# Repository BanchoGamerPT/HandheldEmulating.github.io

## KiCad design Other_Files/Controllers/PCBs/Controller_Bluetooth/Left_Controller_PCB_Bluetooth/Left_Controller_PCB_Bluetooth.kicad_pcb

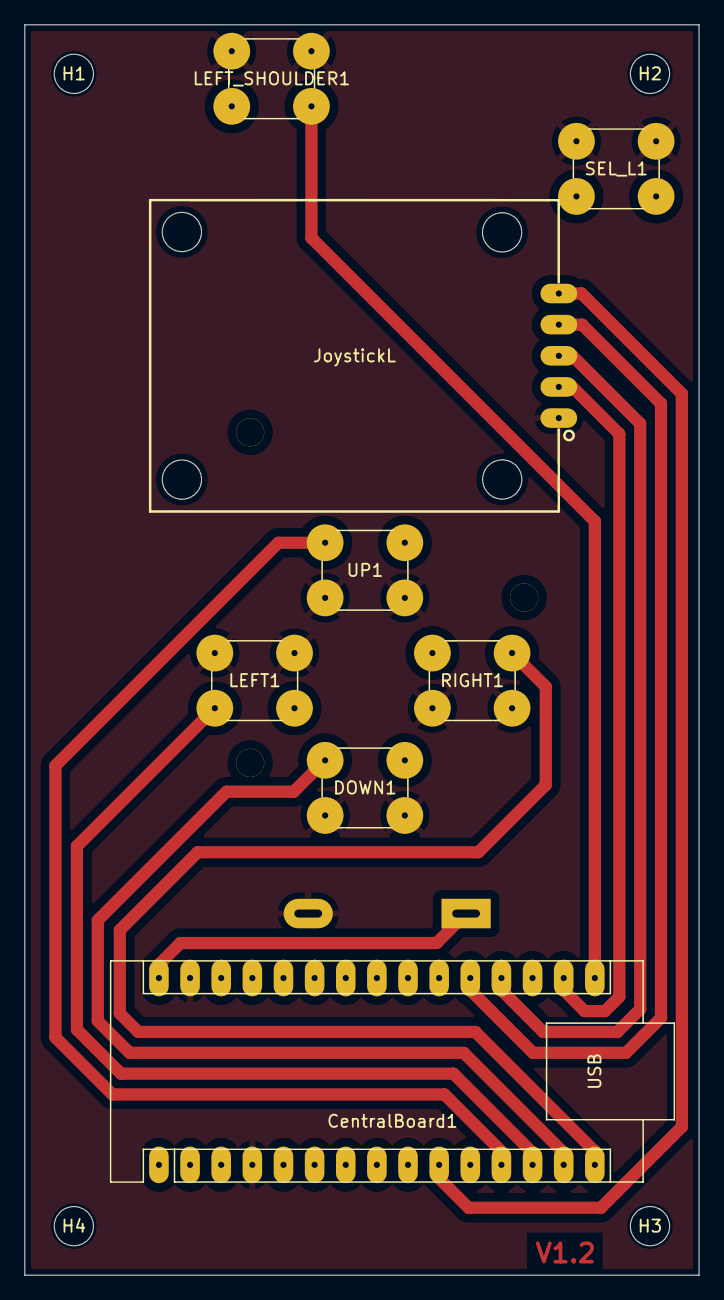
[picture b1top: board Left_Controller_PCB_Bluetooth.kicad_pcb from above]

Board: 2 copper layers, 55.0 x 102.0 mm, 13 parts (1 on the bottom side), 12 nets.

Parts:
BAT9V1: Battery_Cell; BatteryHolder_MPD_BA9VPC_1xPP3
CentralBoard1: Arduino_Nano_v3.x; Arduino_Nano
DOWN1: SW_Push; SW_PUSH_6mm
H1, H2, H3, H4: MountingHole; MountingHole_3.2mm_M3
JoystickL1: JoystickL; Joystick
LEFT1: SW_Push; SW_PUSH_6mm
LEFT_SHOULDER1: SW_Push; SW_PUSH_6mm
RIGHT1: SW_Push; SW_PUSH_6mm
SEL_L1: SW_Push; SW_PUSH_6mm
UP1: SW_Push; SW_PUSH_6mm

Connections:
+3.3V: CentralBoard1.17 (3V3), JoystickL1.2 (+5V)
+9V: BAT9V1.1 (+), CentralBoard1.30 (VIN)
/Analog_X_L: CentralBoard1.19 (A0), JoystickL1.3 (VRX)
/Analog_Y_L: CentralBoard1.20 (A1), JoystickL1.4 (VRY)
/DOWN: CentralBoard1.14 (D11), DOWN1.1
/LEFT: CentralBoard1.13 (D10), LEFT1.2
/LEFT_SHOULDER: CentralBoard1.16 (D13), LEFT_SHOULDER1.1
/RIGHT: CentralBoard1.15 (D12), RIGHT1.1
/SEL_JOY_L: CentralBoard1.10 (D7), JoystickL1.5 (SW)
/SEL_L: CentralBoard1.9 (D6), SEL_L1.1
/UP: CentralBoard1.12 (D9), UP1.1
GND: BAT9V1.2 (-), CentralBoard1.4 (GND), CentralBoard1.29 (GND), DOWN1.2, JoystickL1.1 (GND), LEFT1.1, LEFT_SHOULDER1.2, RIGHT1.2, SEL_L1.2, UP1.2

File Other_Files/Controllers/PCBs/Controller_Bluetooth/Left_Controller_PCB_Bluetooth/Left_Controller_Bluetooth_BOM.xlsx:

Id | Designator | Footprint | Quantity | Designation | Price per piece | Total Price | Datasheet | Link to Parts
1 | JoystickL | Joystick | 1 | KY-023 Joystick Module | 2.5 | 2.5 | https://datasheetspdf.com/pdf-down/K/Y/-/KY-023-Joy-IT.pdf | https://mauser.pt/catalog/product_info.php?products_id=096-9085
2 | LEFT_SHOULDER1, SEL_L1, UP1, , RIGHT1, LEFT1, DOWN1 | SW_PUSH_6mm | 6 | SW_Push | 0.16 | 0.96 | https://mauser.pt/catalog/product_info.php?cPath=324_1401_16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 | https://www.digikey.pt/pt/products/detail/cui-devices/TS02-6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
3 | CentralBoard1 | Arduino_Nano | 1 | Arduino_Nano_v3.x | 19 | 19 | https://docs.arduino.cc/resources/datasheets/ABX00083-datasheet.pdf | https://store.arduino.cc/products/nano-esp32-with-headers
4 | BAT9V1 | BatteryHolder_MPD_BA9VPC_1xPP3 | 1 | Battery Holder 9V | 0.62 | 0.62 | -------------------------------------------------------------------- | https://www.ptrobotics.com/suporte-pilhas/5015-battery-holde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

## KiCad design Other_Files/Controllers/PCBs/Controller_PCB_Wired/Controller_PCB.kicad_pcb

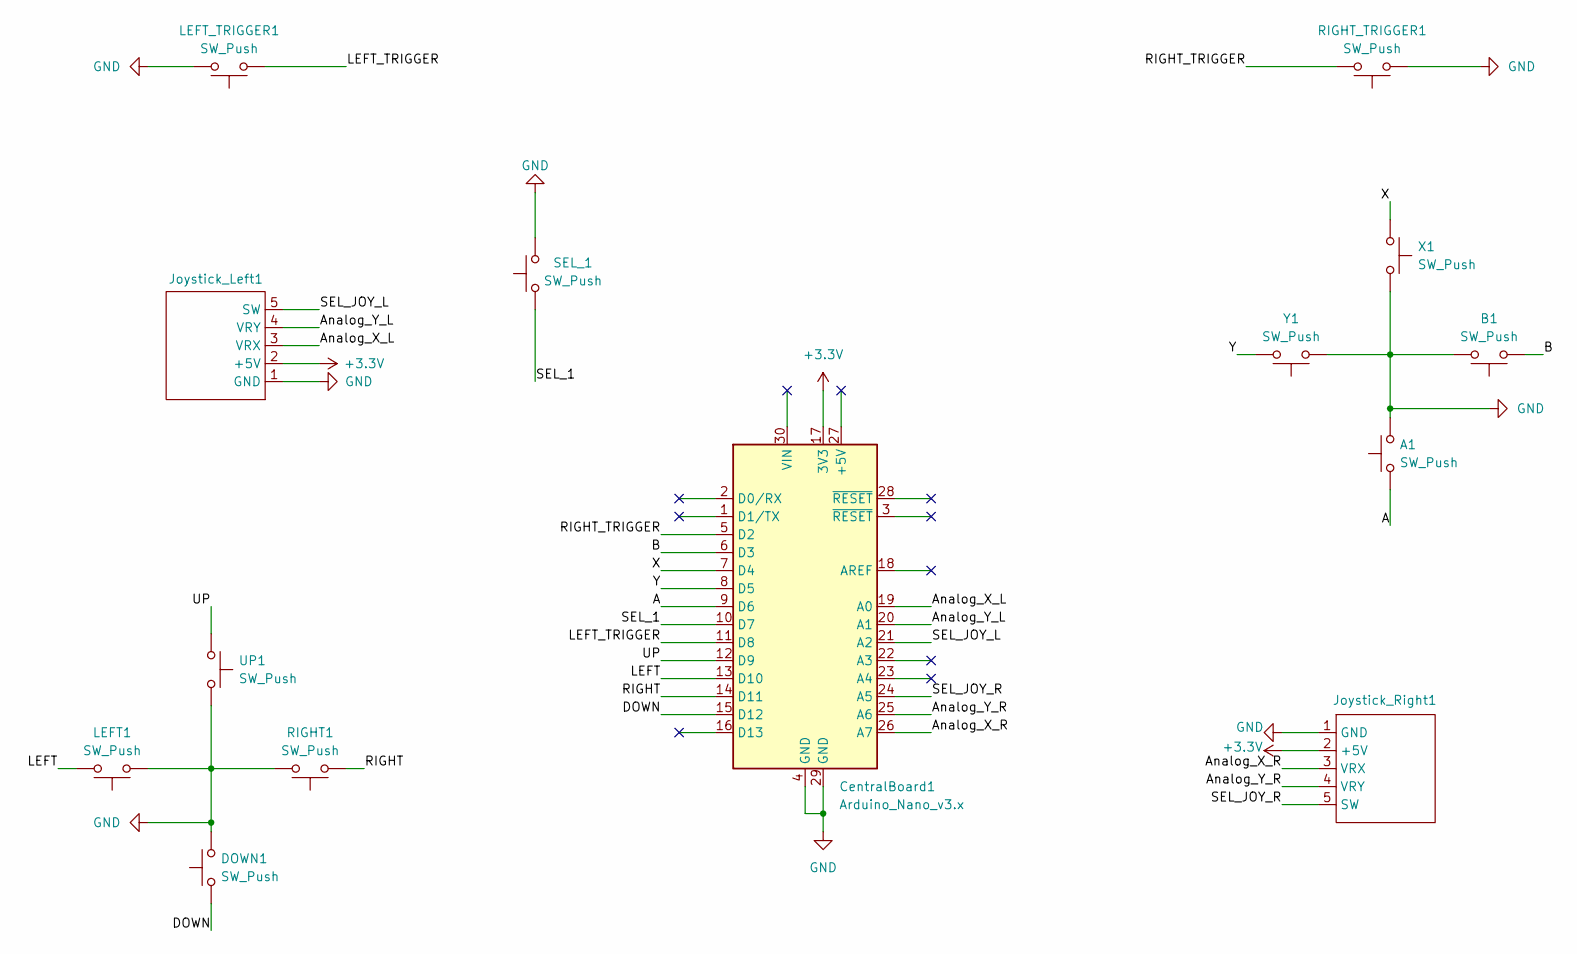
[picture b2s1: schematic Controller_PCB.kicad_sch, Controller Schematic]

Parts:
A1: SW_Push; SW_PUSH_6mm
B1: SW_Push; SW_PUSH_6mm
CentralBoard1: Arduino_Nano_v3.x; Arduino_Nano
DOWN1: SW_Push; SW_PUSH_6mm
Joystick_Left1: Joystick
Joystick_Right1: Joystick
LEFT1: SW_Push; SW_PUSH_6mm
LEFT_TRIGGER1: SW_Push; SW_PUSH_6mm
RIGHT1: SW_Push; SW_PUSH_6mm
RIGHT_TRIGGER1: SW_Push; SW_PUSH_6mm
SEL_1: SW_Push; SW_PUSH_6mm
UP1: SW_Push; SW_PUSH_6mm
X1: SW_Push; SW_PUSH_6mm
Y1: SW_Push; SW_PUSH_6mm

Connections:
+3.3V: CentralBoard1.17 (3V3), Joystick_Left1.2 (+5V), Joystick_Right1.2 (+5V)
/A: A1.1, CentralBoard1.9 (D6)
/Analog_X_L: CentralBoard1.19 (A0), Joystick_Left1.3 (VRX)
/Analog_X_R: CentralBoard1.26 (A7), Joystick_Right1.3 (VRX)
/Analog_Y_L: CentralBoard1.20 (A1), Joystick_Left1.4 (VRY)
/Analog_Y_R: CentralBoard1.25 (A6), Joystick_Right1.4 (VRY)
/B: B1.1, CentralBoard1.6 (D3)
/DOWN: CentralBoard1.15 (D12), DOWN1.1
/LEFT: CentralBoard1.13 (D10), LEFT1.2
/LEFT_TRIGGER: CentralBoard1.11 (D8), LEFT_TRIGGER1.1
/RIGHT: CentralBoard1.14 (D11), RIGHT1.1
/RIGHT_TRIGGER: CentralBoard1.5 (D2), RIGHT_TRIGGER1.2
/SEL_1: CentralBoard1.10 (D7), SEL_1.1
/SEL_JOY_L: CentralBoard1.21 (A2), Joystick_Left1.5 (SW)
/SEL_JOY_R: CentralBoard1.24 (A5), Joystick_Right1.5 (SW)
/UP: CentralBoard1.12 (D9), UP1.1
/X: CentralBoard1.7 (D4), X1.1
/Y: CentralBoard1.8 (D5), Y1.2
GND: A1.2, B1.2, CentralBoard1.4 (GND), CentralBoard1.29 (GND), DOWN1.2, Joystick_Left1.1 (GND), Joystick_Right1.1 (GND), LEFT1.1, LEFT_TRIGGER1.2, RIGHT1.2, RIGHT_TRIGGER1.1, SEL_1.2, UP1.2, X1.2, Y1.1

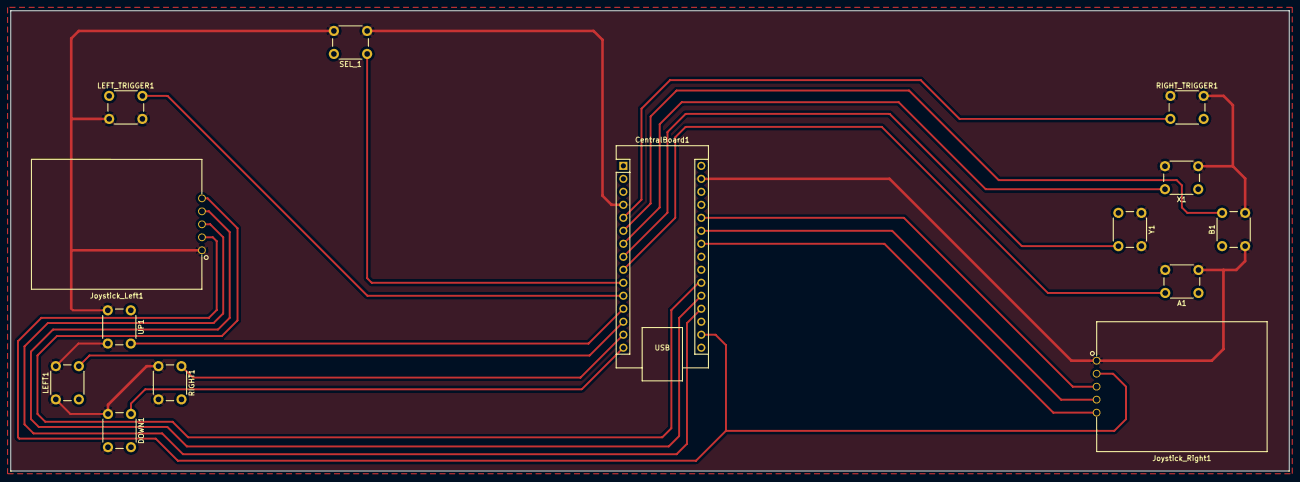
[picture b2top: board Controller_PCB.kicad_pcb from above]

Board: 2 copper layers, 250.0 x 90.0 mm, 14 parts (0 on the bottom side), 19 nets.

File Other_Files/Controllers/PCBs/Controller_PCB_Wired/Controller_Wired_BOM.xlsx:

Id | Designator | Footprint | Quantity | Designation | Price per piece | Total Price | Datasheet | Link to Parts
1 | Joystick_Left1, Joystick_Right1 | Joystick | 2 | KY-023 Joystick Module | 2.5 | 5 | https://datasheetspdf.com/pdf-down/K/Y/-/KY-023-Joy-IT.pdf | https://mauser.pt/catalog/product_info.php?products_id=096-9085
2 | RIGHT_TRIGGER1, LEFT_TRIGGER1, Y1, X1, UP1, SEL_1, RIGHT1, LEFT1, DOWN1, B1, A1 | SW_PUSH_6mm | 11 | SW_Push | 0.16 | 1.76 | https://www.farnell.com/datasheets/2343587.pdf | https://www.digikey.pt/pt/products/detail/cui-devices/TS02-6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
3 | CentralBoard1 | Arduino_Nano | 1 | Arduino_Nano_v3.x | 19 | 19 | https://docs.arduino.cc/resources/datasheets/ABX00083-datasheet.pdf | https://store.arduino.cc/products/nano-esp32-with-headers

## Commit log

2024-03-30 Updated the Blog
2024-04-03 Updated Changelog and links now go to blank tabs
2024-04-03 Added a Downloads tab!
2024-04-19 Inserted who was present in each update
2024-04-19 Added a new update about the mid-term presentation
2024-04-20 updated the project proposal to the mid-term one
2024-04-22 Planning PDF now properly appears
2024-04-22 Updated electrocap demo day
2024-04-24 Update 22
2024-04-26 trying to fix something
2024-04-26 I think i fixed it
2024-05-02 Update 23
2024-05-02 update 24
    we did it
2024-05-05 Updates 25, 26 and 27
    Note: 27 is unfinished
2024-05-06 Finished Update 27
    Added the video for the update
2024-05-07 Update 28
2024-05-08 Update 29 and some product.html changes
2024-05-08 Created Inquiry page
2024-05-08 Changed the name of the Project
    Changed the name of the Project to Handheld Digital Emulating Console [HDEC] (much cooler)
2024-05-08 Wrote some part of the inquiry.html and changed image directory
2024-05-08 Inserted Inquiry Data
    Updated inquiry.html
2024-05-08 Added conclusions to graphs
    Updated inquiry.html
2024-05-08 Added some materials to material list
2024-05-08 Update 30
    Automatização do teste de CI's
2024-05-08 Updated update 30
2024-05-11 Added Arduino Sketch
    Added Arduino sketch with the CI test
2024-05-11 Updated link to Sketch
    O link para download do sketch para teste para o circuito integrado já funciona
2024-05-11 Added PCB Files to repository
2024-05-11 Changes the location of some files
2024-05-12 Updates 31 and 32
2024-05-12 Updated clarity on Downloads text
2024-05-12 Updated the Controllers' PCB to version 1.2
2024-05-12 corrected previous commit
2024-05-12 Updated 33
2024-05-21 Updated Bluetooth Controllers' PCBs
2024-05-21 Updates 34 to 37
2024-05-22 Added the forgotten update (now update 34) and new update 39
2024-05-22 resolving lower to upper case images
2024-05-22 resolving lower to uppercase images
2024-05-31 fixed index.html image
2024-06-01 Updates 40, 41 and 42
    Still missing 2 images on update 41
2024-06-05 Various Updates
2024-06-05 Changed Update 20
2024-06-07 Updated media sizes
2024-06-07 Video and Case Updates
2024-06-07 Updated Video Editing Image
2024-06-07 Corrected people in update
2024-06-07 Added some more material information
2024-06-07 Product page changes
2024-06-28 Updated downloads.html
    (missing links)
2024-06-28 Changed case files location
2024-06-28 Updated links on downloads.html
2024-06-28 Updates 53, 54 and 55
2024-06-28 Changed latest changelog on index page
2024-06-30 Added the rest of the files
2024-06-30 Corrected Links
2024-06-30 Rename Use Customized MiSTer Menu.md to README.md
2024-06-30 Rename README.md to HOW_TO.md
2024-06-30 Revert "Rename README.md to HOW_TO.md"
    This reverts commit 0d82289ccf9a086f7755ee5059ed90abd809f072.
2024-06-30 Increased some text size on README.md
2024-06-30 Now it's bold instead of header
2024-06-30 And also highlighted
2024-06-30 Revert "And also highlighted"
    This reverts commit 8188619f181fa107fc2e627bb332c8520d1bbab9.
